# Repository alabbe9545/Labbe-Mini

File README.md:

# Labbe-Mini

This is a project that helped me learn how to make keyboards, this might also help anyone thinking of making their own PCB.

Before opening it on Kicad download the following libraries and place them in the root folder inside ExtLibraries folder (create the folder):
* https://github.com/KiCad/Housings_QFP.pretty (should be named Housings_QFP.pretty)
* https://github.com/tmk/keyboard_parts.pretty (should be named keyboard_parts.pretty)
* https://github.com/tmk/kicad_lib_tmk (should be named kicad_lib_tmk-master)
* https://github.com/sszczep/kicad-libraries (should be named kicad-libraries-master)

Some nice pictures of the keyboard

Pieces needed
* 4 x WS2812B 5050 RGB LEDs (https://aliexpress.com/item/1005002653014067.html?gatewayAdapt=glo2deu&spm=a2g0o.9042311.0.0.55134c4dMfKc13)
* 4 x Kaihl Hotswap sockets (https://aliexpress.com/item/32951252318.html?gatewayAdapt=glo2deu&spm=a2g0o.9042311.0.0.55134c4dMfKc13)
* 4 x Compatible mechanical switches (Cherry, Kaihl, etc)
* 1 x Atmega32U4 (https://www.digikey.de/de/products/detail/microchip-technology/ATMEGA32U4-AUR/2238241)
* 4 x Diodes (https://www.digikey.de/de/products/detail/taiwan-semiconductor-corporation/1N4148W-G-RHG/7374103)
* 2 x 22 Ohm Resistors (https://www.digikey.de/de/products/detail/stackpole-electronics-inc/RMCF0805JT22R0/1757897)
* 2 x 10k Ohm Resistors (https://www.digikey.de/de/products/detail/stackpole-electronics-inc/RMCF0805JT10K0/1757762)
* 1 x 330 Ohm Resistor (https://www.digikey.de/de/products/detail/stackpole-electronics-inc/RMCF0805FT330R/1760484)
* 2 x 5.1k Ohm Resistor (https://www.digikey.de/de/products/detail/stackpole-electronics-inc/RMCF0805JT5K10/1757930)
* 8 x 0.1uF Capacitors (https://www.digikey.de/de/products/detail/yageo/CC0805ZRY5V9BB104/2103099)
* 1 x 1uF Capacitor (https://www.digikey.de/de/products/detail/yageo/CC0805KKX7R7BB105/2103103)
* 1 x Button (https://www.digikey.de/de/products/detail/e-switch/TL3342F160QG-TR/379003)
* 2 x 22pF Capacitors (https://www.digikey.de/de/products/detail/kemet/C0805C220J5GAC7800/411112)
* 1 x 4.7uF Capacitor (https://www.digikey.de/de/products/detail/murata-electronics/GRM219R61E475KA73D/4905426)
* 1 x 16MHZ Quartz Crystal (https://www.digikey.de/de/products/detail/ecs-inc/ECS-160-18-33-AEN-TR/8023240)
* 1 x USB-C - USB2 Receptacle (https://www.digikey.de/de/products/detail/gct/USB4085-GF-A/9859662)

Thanks to:
* ai03-2725, to be able to fit the WS2812B 5050 RGB LEDs i modified the footprints of https://github.com/ai03-2725/MX_Alps_Hybrid
* The creator of the nice silkscreen image, euphoria (https://twitter.com/3uf0ria) (https://www.pixiv.net/en/users/17700641).
* QMK Firmware ( https://github.com/qmk/qmk_firmware/tree/master/keyboards/labbe/labbeminiv1 ).

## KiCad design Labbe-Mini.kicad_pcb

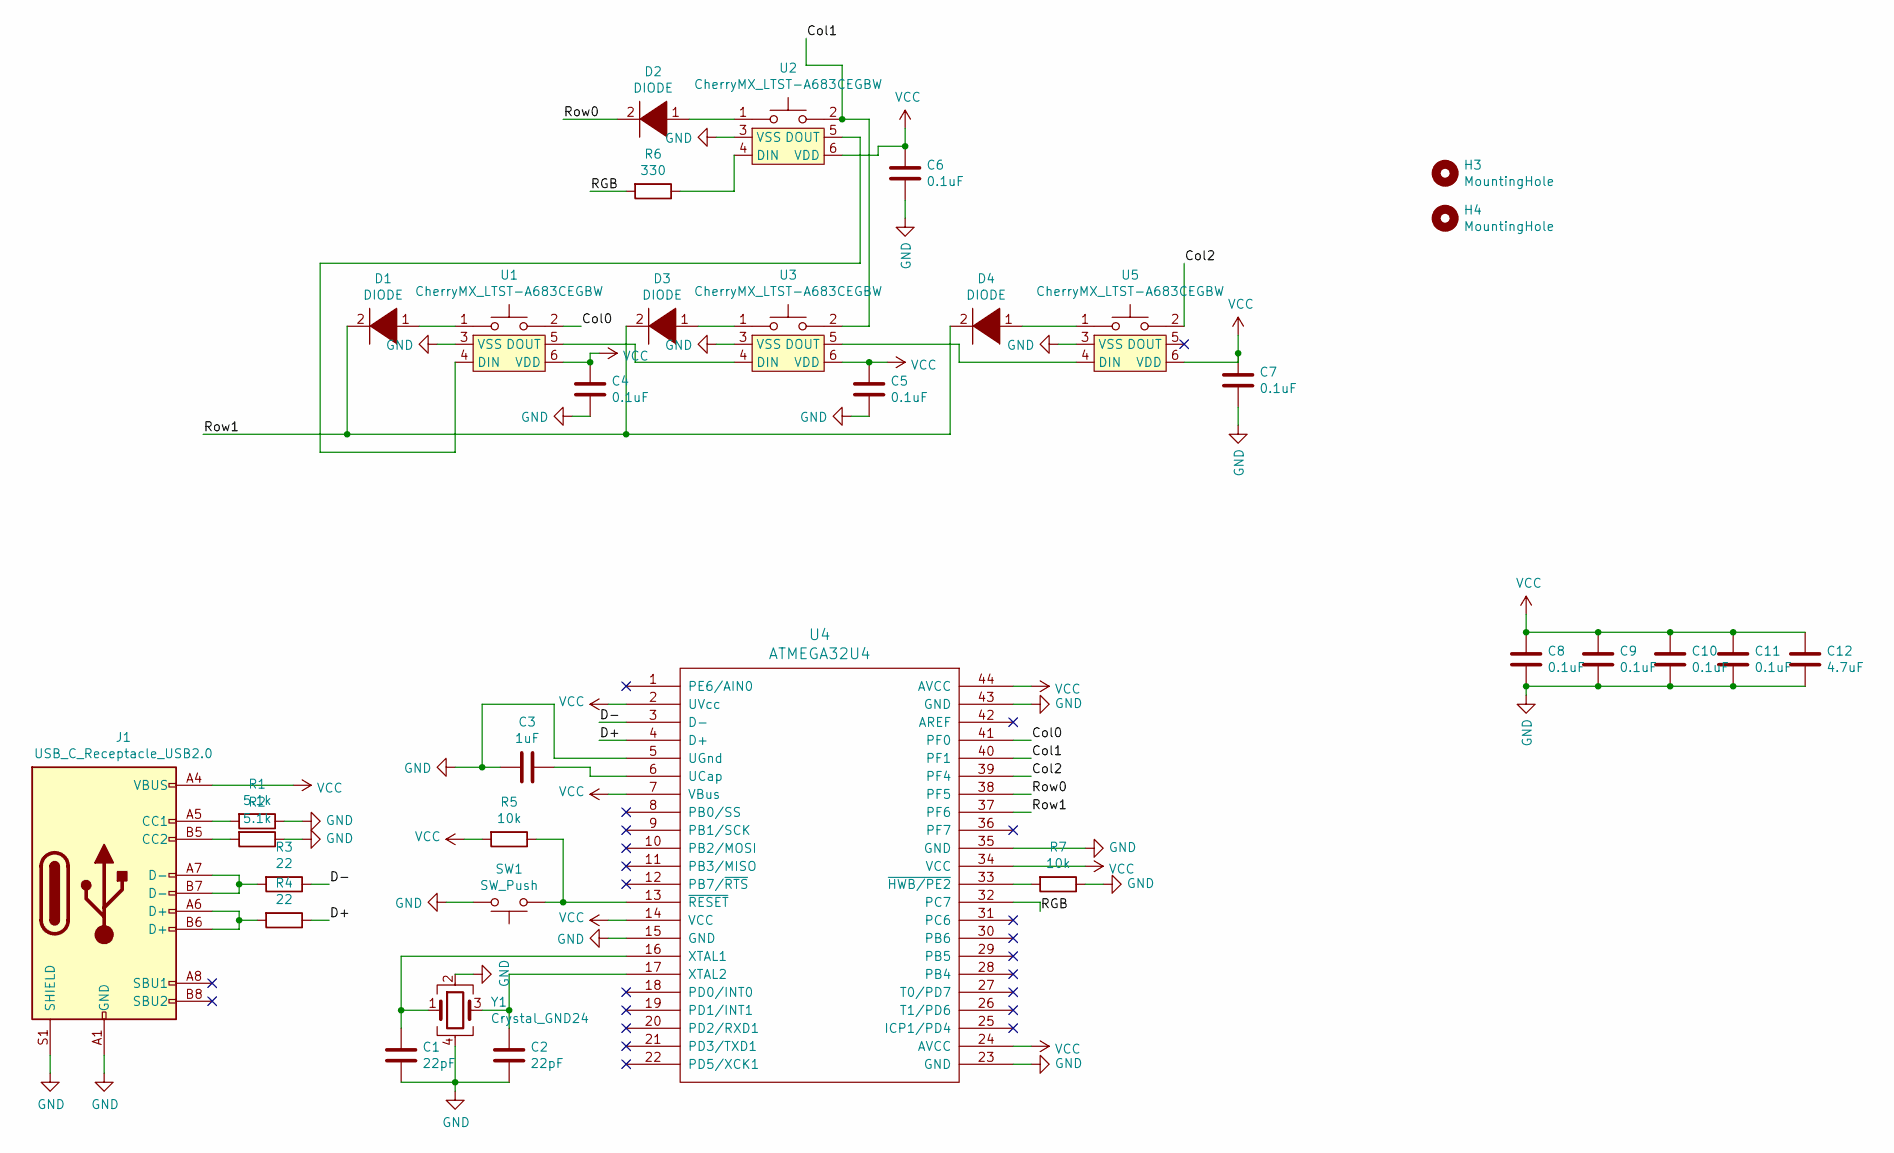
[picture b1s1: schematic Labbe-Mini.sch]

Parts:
C1, C2: 22pF; C_0805_2012Metric_Pad1.18x1.45mm_HandSolder
C3: 1uF; C_0805_2012Metric_Pad1.18x1.45mm_HandSolder
C4, C5, C6, C7, C8, C9, C10, C11: 0.1uF; C_0805_2012Metric_Pad1.18x1.45mm_HandSolder
C12: 4.7uF; C_0805_2012Metric_Pad1.18x1.45mm_HandSolder
D1, D2, D3, D4: DIODE; D_SOD123_axial
H3, H4: MountingHole; MountingHole_2.1mm
J1: USB_C_Receptacle_USB2.0; USB_C_Receptacle_GCT_USB4085
R1, R2: 5.1k; R_0805_2012Metric_Pad1.20x1.40mm_HandSolder
R3, R4: 22; R_0805_2012Metric_Pad1.20x1.40mm_HandSolder
R5, R7: 10k; R_0805_2012Metric_Pad1.20x1.40mm_HandSolder
R6: 330; R_0805_2012Metric_Pad1.20x1.40mm_HandSolder
SW1: SW_Push; SW_SPST_TL3342
U1, U2, U3, U5: CherryMX_LTST-A683CEGBW; MXOnly-1U-Hotswap
U4: ATMEGA32U4; TQFP-44_10x10mm_Pitch0.8mm
Y1: Crystal_GND24; Crystal_SMD_3225-4Pin_3.2x2.5mm

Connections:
/Col0: U1.2, U4.41 (PF0)
/Col1: U2.2, U3.2, U4.40 (PF1)
/Col2: U4.39 (PF4), U5.2
/D+: R4.1, U4.4 (D+)
/D-: R3.1, U4.3 (D-)
/RGB: R6.2, U4.32 (PC7)
/Row0: D2.2 (A), U4.38 (PF5)
/Row1: D1.2 (A), D3.2 (A), D4.2 (A), U4.37 (PF6)
GND: C1.2, C2.2, C3.1, C4.2, C5.2, C6.2, C7.2, C8.2, C9.2, C10.2, C11.2, C12.2, J1.A1 (GND), J1.A12 (GND), J1.B1 (GND), J1.B12 (GND), J1.S1 (SHIELD), R1.1, R2.1, R7.1, SW1.2, U1.3 (VSS), U2.3 (VSS), U3.3 (VSS), U4.5 (UGnd), U4.15 (GND), U4.23 (GND), U4.35 (GND), U4.43 (GND), U5.3 (VSS), Y1.2, Y1.4
unnamed: C1.1, U4.16 (XTAL1), Y1.1
unnamed: C2.1, U4.17 (XTAL2), Y1.3
unnamed: C3.2, U4.6 (UCap)
unnamed: D1.1 (K), U1.1
unnamed: D2.1 (K), U2.1
unnamed: D3.1 (K), U3.1
unnamed: D4.1 (K), U5.1
unnamed: J1.A5 (CC1), R1.2
unnamed: J1.A6 (D+), J1.B6 (D+), R4.2
unnamed: J1.A7 (D-), J1.B7 (D-), R3.2
unnamed: J1.B5 (CC2), R2.2
unnamed: R5.1, SW1.1, U4.13 (~RESET)
unnamed: R6.1, U2.4 (DIN)
unnamed: R7.2, U4.33 (~HWB/PE2)
unnamed: U1.4 (DIN), U2.5 (DOUT)
unnamed: U1.5 (DOUT), U3.4 (DIN)
unnamed: U3.5 (DOUT), U5.4 (DIN)
VCC: C4.1, C5.1, C6.1, C7.1, C8.1, C9.1, C10.1, C11.1, C12.1, J1.A4 (VBUS), J1.A9 (VBUS), J1.B4 (VBUS), J1.B9 (VBUS), R5.2, U1.6 (VDD), U2.6 (VDD), U3.6 (VDD), U4.2 (UVcc), U4.7 (VBus), U4.14 (VCC), U4.24 (AVCC), U4.34 (VCC), U4.44 (AVCC), U5.6 (VDD)

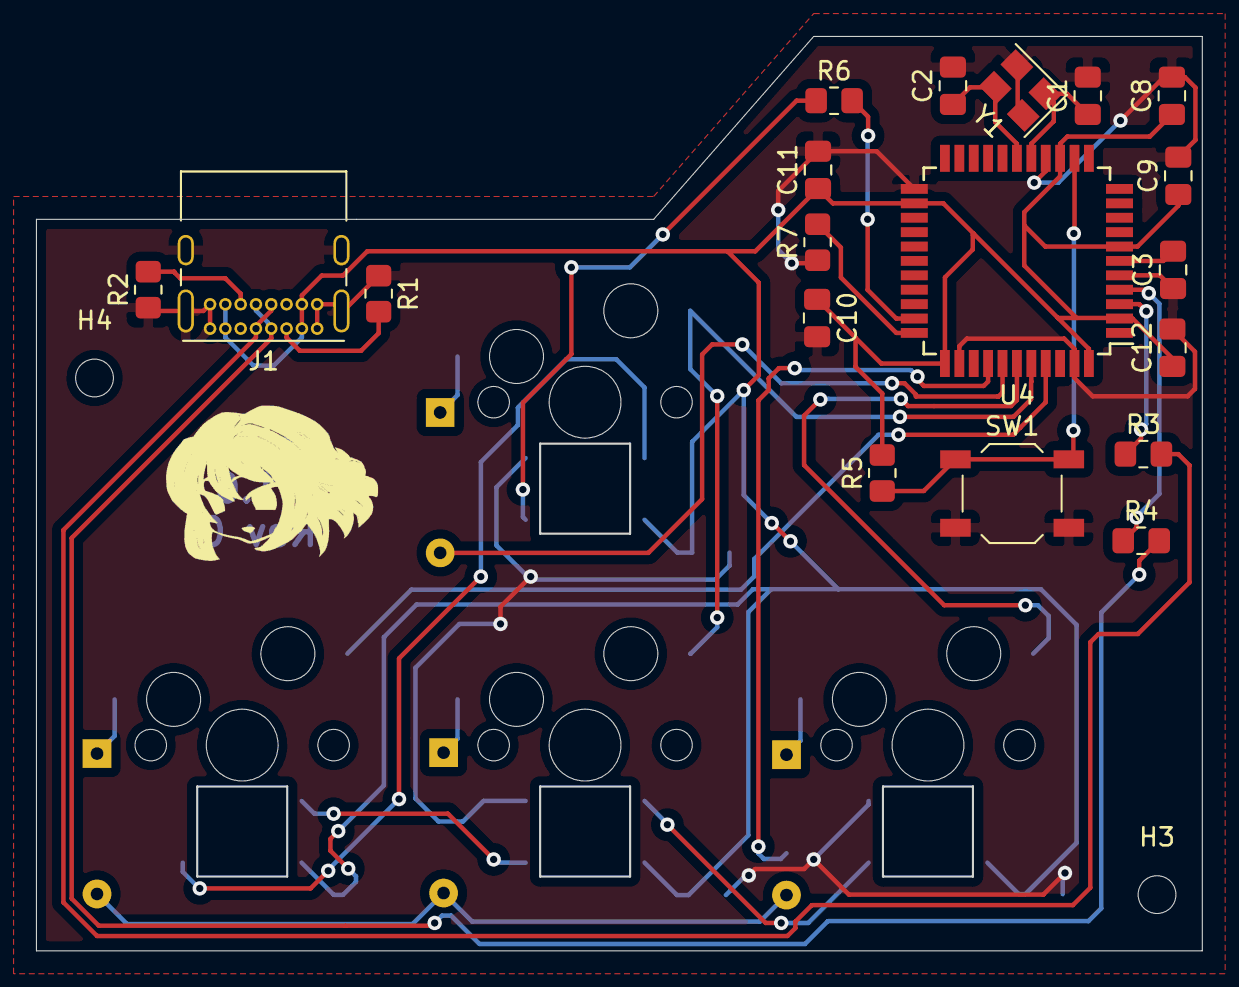
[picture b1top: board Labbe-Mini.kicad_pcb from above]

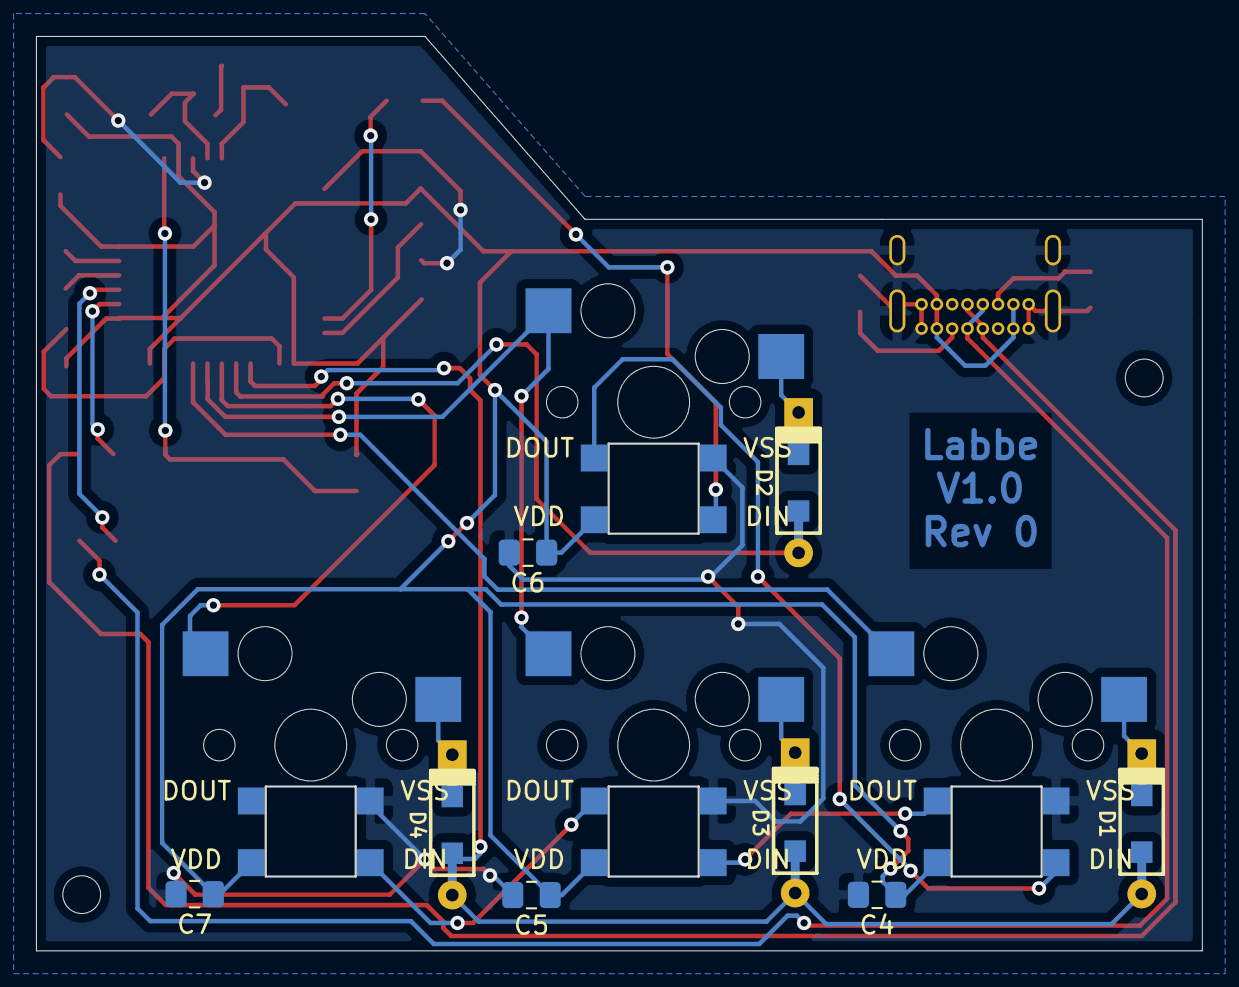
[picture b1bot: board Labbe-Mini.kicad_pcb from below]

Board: 2 copper layers, 64.7 x 50.7 mm, 33 parts (8 on the bottom side), 27 nets.

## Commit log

2022-02-19 Main - Added images of the PCB
2022-02-19 Main - Added new images - Modified Readme
2022-02-19 main - Added more images to the readme - Added more thanks
2022-02-19 main - Rotated 2 images
2022-02-19 main - Updated status on QMK and artist
2022-02-19 main - Added artist info
2022-06-14 Adding keyboard case
2022-06-14 Added case pic
2023-02-18 Removed waiting to be merged to QMK from Readme because i already got merged
